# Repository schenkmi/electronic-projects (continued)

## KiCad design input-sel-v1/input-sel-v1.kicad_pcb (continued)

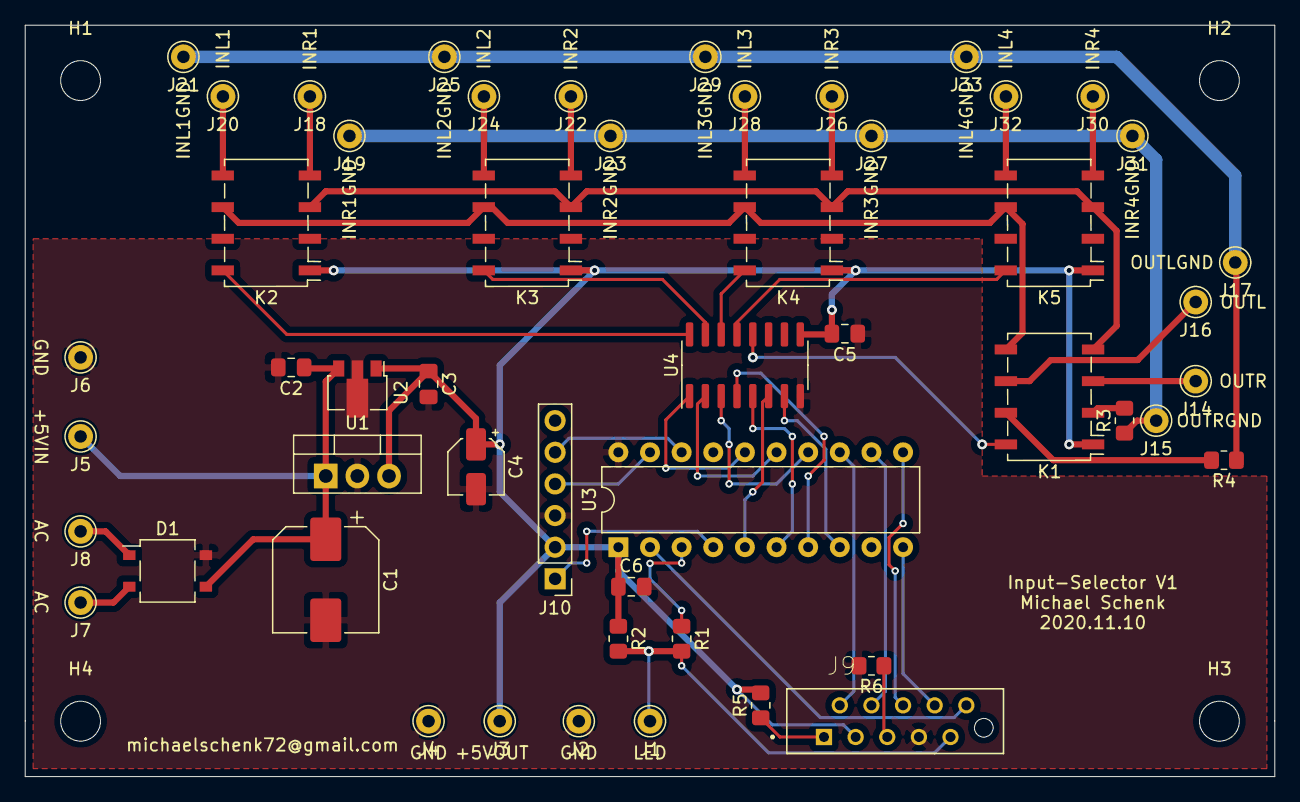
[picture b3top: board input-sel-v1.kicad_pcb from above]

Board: 2 copper layers, 100.3 x 60.3 mm, 56 parts (0 on the bottom side), 45 nets.

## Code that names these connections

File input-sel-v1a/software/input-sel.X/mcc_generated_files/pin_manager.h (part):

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// get/set IO_RA4 aliases
#define IO_RA4_TRIS                 TRISAbits.TRISA4
#define IO_RA4_LAT                  LATAbits.LATA4
#define IO_RA4_PORT                 PORTAbits.RA4
#define IO_RA4_WPU                  WPUAbits.WPUA4
#define IO_RA4_OD                   ODCONAbits.ODCA4
#define IO_RA4_ANS                  ANSELAbits.ANSA4
#define IO_RA4_SetHigh()            do { LATAbits.LATA4 = 1; } while(0)
#define IO_RA4_SetLow()             do { LATAbits.LATA4 = 0; } while(0)
#define IO_RA4_Toggle()             do { LATAbits.LATA4 = ~LATAbits.LATA4; } while(0)
#define IO_RA4_GetValue()           PORTAbits.RA4
#define IO_RA4_SetDigitalInput()    do { TRISAbits.TRISA4 = 1; } while(0)
#define IO_RA4_SetDigitalOutput()   do { TRISAbits.TRISA4 = 0; } while(0)
#define IO_RA4_SetPullup()          do { WPUAbits.WPUA4 = 1; } while(0)
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// get/set IO_RA5 aliases
#define IO_RA5_TRIS                 TRISAbits.TRISA5
#define IO_RA5_LAT                  LATAbits.LATA5
#define IO_RA5_PORT                 PORTAbits.RA5
#define IO_RA5_WPU                  WPUAbits.WPUA5
#define IO_RA5_OD                   ODCONAbits.ODCA5
#define IO_RA5_ANS                  ANSELAbits.ANSA5
#define IO_RA5_SetHigh()            do { LATAbits.LATA5 = 1; } while(0)
#define IO_RA5_SetLow()             do { LATAbits.LATA5 = 0; } while(0)
#define IO_RA5_Toggle()             do { LATAbits.LATA5 = ~LATAbits.LATA5; } while(0)
#define IO_RA5_GetValue()           PORTAbits.RA5
#define IO_RA5_SetDigitalInput()    do { TRISAbits.TRISA5 = 1; } while(0)
#define IO_RA5_SetDigitalOutput()   do { TRISAbits.TRISA5 = 0; } while(0)
#define IO_RA5_SetPullup()          do { WPUAbits.WPUA5 = 1; } while(0)
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// get/set IO_RB4 aliases
#define IO_RB4_TRIS                 TRISBbits.TRISB4
#define IO_RB4_LAT                  LATBbits.LATB4
#define IO_RB4_PORT                 PORTBbits.RB4
#define IO_RB4_WPU                  WPUBbits.WPUB4
#define IO_RB4_OD                   ODCONBbits.ODCB4
#define IO_RB4_ANS                  ANSELBbits.ANSB4
#define IO_RB4_SetHigh()            do { LATBbits.LATB4 = 1; } while(0)
#define IO_RB4_SetLow()             do { LATBbits.LATB4 = 0; } while(0)
#define IO_RB4_Toggle()             do { LATBbits.LATB4 = ~LATBbits.LATB4; } while(0)
#define IO_RB4_GetValue()           PORTBbits.RB4
#define IO_RB4_SetDigitalInput()    do { TRISBbits.TRISB4 = 1; } while(0)
#define IO_RB4_SetDigitalOutput()   do { TRISBbits.TRISB4 = 0; } while(0)
#define IO_RB4_SetPullup()          do { WPUBbits.WPUB4 = 1; } while(0)
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// get/set IO_RB5 aliases
#define IO_RB5_TRIS                 TRISBbits.TRISB5
#define IO_RB5_LAT                  LATBbits.LATB5
#define IO_RB5_PORT                 PORTBbits.RB5
#define IO_RB5_WPU                  WPUBbits.WPUB5
#define IO_RB5_OD                   ODCONBbits.ODCB5
#define IO_RB5_ANS                  ANSELBbits.ANSB5
#define IO_RB5_SetHigh()            do { LATBbits.LATB5 = 1; } while(0)
#define IO_RB5_SetLow()             do { LATBbits.LATB5 = 0; } while(0)
#define IO_RB5_Toggle()             do { LATBbits.LATB5 = ~LATBbits.LATB5; } while(0)
#define IO_RB5_GetValue()           PORTBbits.RB5
#define IO_RB5_SetDigitalInput()    do { TRISBbits.TRISB5 = 1; } while(0)
#define IO_RB5_SetDigitalOutput()   do { TRISBbits.TRISB5 = 0; } while(0)
#define IO_RB5_SetPullup()          do { WPUBbits.WPUB5 = 1; } while(0)
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// get/set IO_RB6 aliases
#define IO_RB6_TRIS                 TRISBbits.TRISB6
#define IO_RB6_LAT                  LATBbits.LATB6
#define IO_RB6_PORT                 PORTBbits.RB6
#define IO_RB6_WPU                  WPUBbits.WPUB6
#define IO_RB6_OD                   ODCONBbits.ODCB6
#define IO_RB6_ANS                  ANSELBbits.ANSB6
#define IO_RB6_SetHigh()            do { LATBbits.LATB6 = 1; } while(0)
#define IO_RB6_SetLow()             do { LATBbits.LATB6 = 0; } while(0)
#define IO_RB6_Toggle()             do { LATBbits.LATB6 = ~LATBbits.LATB6; } while(0)
#define IO_RB6_GetValue()           PORTBbits.RB6
#define IO_RB6_SetDigitalInput()    do { TRISBbits.TRISB6 = 1; } while(0)
#define IO_RB6_SetDigitalOutput()   do { TRISBbits.TRISB6 = 0; } while(0)
#define IO_RB6_SetPullup()          do { WPUBbits.WPUB6 = 1; } while(0)
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// get/set IO_RB7 aliases
#define IO_RB7_TRIS                 TRISBbits.TRISB7
#define IO_RB7_LAT                  LATBbits.LATB7
#define IO_RB7_PORT                 PORTBbits.RB7
#define IO_RB7_WPU                  WPUBbits.WPUB7
#define IO_RB7_OD                   ODCONBbits.ODCB7
#define IO_RB7_ANS                  ANSELBbits.ANSB7
#define IO_RB7_SetHigh()            do { LATBbits.LATB7 = 1; } while(0)
#define IO_RB7_SetLow()             do { LATBbits.LATB7 = 0; } while(0)
#define IO_RB7_Toggle()             do { LATBbits.LATB7 = ~LATBbits.LATB7; } while(0)
#define IO_RB7_GetValue()           PORTBbits.RB7
#define IO_RB7_SetDigitalInput()    do { TRISBbits.TRISB7 = 1; } while(0)
#define IO_RB7_SetDigitalOutput()   do { TRISBbits.TRISB7 = 0; } while(0)
#define IO_RB7_SetPullup()          do { WPUBbits.WPUB7 = 1; } while(0)
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// get/set IO_RC0 aliases
#define IO_RC0_TRIS                 TRISCbits.TRISC0
#define IO_RC0_LAT                  LATCbits.LATC0
#define IO_RC0_PORT                 PORTCbits.RC0
#define IO_RC0_WPU                  WPUCbits.WPUC0
#define IO_RC0_OD                   ODCONCbits.ODCC0
#define IO_RC0_ANS                  ANSELCbits.ANSC0
#define IO_RC0_SetHigh()            do { LATCbits.LATC0 = 1; } while(0)
#define IO_RC0_SetLow()             do { LATCbits.LATC0 = 0; } while(0)
#define IO_RC0_Toggle()             do { LATCbits.LATC0 = ~LATCbits.LATC0; } while(0)
#define IO_RC0_GetValue()           PORTCbits.RC0
#define IO_RC0_SetDigitalInput()    do { TRISCbits.TRISC0 = 1; } while(0)
#define IO_RC0_SetDigitalOutput()   do { TRISCbits.TRISC0 = 0; } while(0)
#define IO_RC0_SetPullup()          do { WPUCbits.WPUC0 = 1; } while(0)
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// get/set IO_RC1 aliases
#define IO_RC1_TRIS                 TRISCbits.TRISC1
#define IO_RC1_LAT                  LATCbits.LATC1
#define IO_RC1_PORT                 PORTCbits.RC1
#define IO_RC1_WPU                  WPUCbits.WPUC1
#define IO_RC1_OD                   ODCONCbits.ODCC1
#define IO_RC1_ANS                  ANSELCbits.ANSC1
#define IO_RC1_SetHigh()            do { LATCbits.LATC1 = 1; } while(0)
#define IO_RC1_SetLow()             do { LATCbits.LATC1 = 0; } while(0)
#define IO_RC1_Toggle()             do { LATCbits.LATC1 = ~LATCbits.LATC1; } while(0)
#define IO_RC1_GetValue()           PORTCbits.RC1
#define IO_RC1_SetDigitalInput()    do { TRISCbits.TRISC1 = 1; } while(0)
#define IO_RC1_SetDigitalOutput()   do { TRISCbits.TRISC1 = 0; } while(0)
#define IO_RC1_SetPullup()          do { WPUCbits.WPUC1 = 1; } while(0)
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// get/set IO_RC2 aliases
#define IO_RC2_TRIS                 TRISCbits.TRISC2
#define IO_RC2_LAT                  LATCbits.LATC2
#define IO_RC2_PORT                 PORTCbits.RC2
#define IO_RC2_WPU                  WPUCbits.WPUC2
#define IO_RC2_OD                   ODCONCbits.ODCC2
#define IO_RC2_ANS                  ANSELCbits.ANSC2
#define IO_RC2_SetHigh()            do { LATCbits.LATC2 = 1; } while(0)
#define IO_RC2_SetLow()             do { LATCbits.LATC2 = 0; } while(0)
#define IO_RC2_Toggle()             do { LATCbits.LATC2 = ~LATCbits.LATC2; } while(0)
#define IO_RC2_GetValue()           PORTCbits.RC2
#define IO_RC2_SetDigitalInput()    do { TRISCbits.TRISC2 = 1; } while(0)
#define IO_RC2_SetDigitalOutput()   do { TRISCbits.TRISC2 = 0; } while(0)
#define IO_RC2_SetPullup()          do { WPUCbits.WPUC2 = 1; } while(0)
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// get/set IO_RC3 aliases
#define IO_RC3_TRIS                 TRISCbits.TRISC3
#define IO_RC3_LAT                  LATCbits.LATC3
#define IO_RC3_PORT                 PORTCbits.RC3
#define IO_RC3_WPU                  WPUCbits.WPUC3
#define IO_RC3_OD                   ODCONCbits.ODCC3
#define IO_RC3_ANS                  ANSELCbits.ANSC3
#define IO_RC3_SetHigh()            do { LATCbits.LATC3 = 1; } while(0)
#define IO_RC3_SetLow()             do { LATCbits.LATC3 = 0; } while(0)
#define IO_RC3_Toggle()             do { LATCbits.LATC3 = ~LATCbits.LATC3; } while(0)
#define IO_RC3_GetValue()           PORTCbits.RC3
#define IO_RC3_SetDigitalInput()    do { TRISCbits.TRISC3 = 1; } while(0)
#define IO_RC3_SetDigitalOutput()   do { TRISCbits.TRISC3 = 0; } while(0)
#define IO_RC3_SetPullup()          do { WPUCbits.WPUC3 = 1; } while(0)
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// get/set IO_RC4 aliases
#define IO_RC4_TRIS                 TRISCbits.TRISC4
#define IO_RC4_LAT                  LATCbits.LATC4
#define IO_RC4_PORT                 PORTCbits.RC4
#define IO_RC4_WPU                  WPUCbits.WPUC4
#define IO_RC4_OD                   ODCONCbits.ODCC4
#define IO_RC4_ANS                  ANSELCbits.ANSC4
#define IO_RC4_SetHigh()            do { LATCbits.LATC4 = 1; } while(0)
#define IO_RC4_SetLow()             do { LATCbits.LATC4 = 0; } while(0)
#define IO_RC4_Toggle()             do { LATCbits.LATC4 = ~LATCbits.LATC4; } while(0)
#define IO_RC4_GetValue()           PORTCbits.RC4
#define IO_RC4_SetDigitalInput()    do { TRISCbits.TRISC4 = 1; } while(0)
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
